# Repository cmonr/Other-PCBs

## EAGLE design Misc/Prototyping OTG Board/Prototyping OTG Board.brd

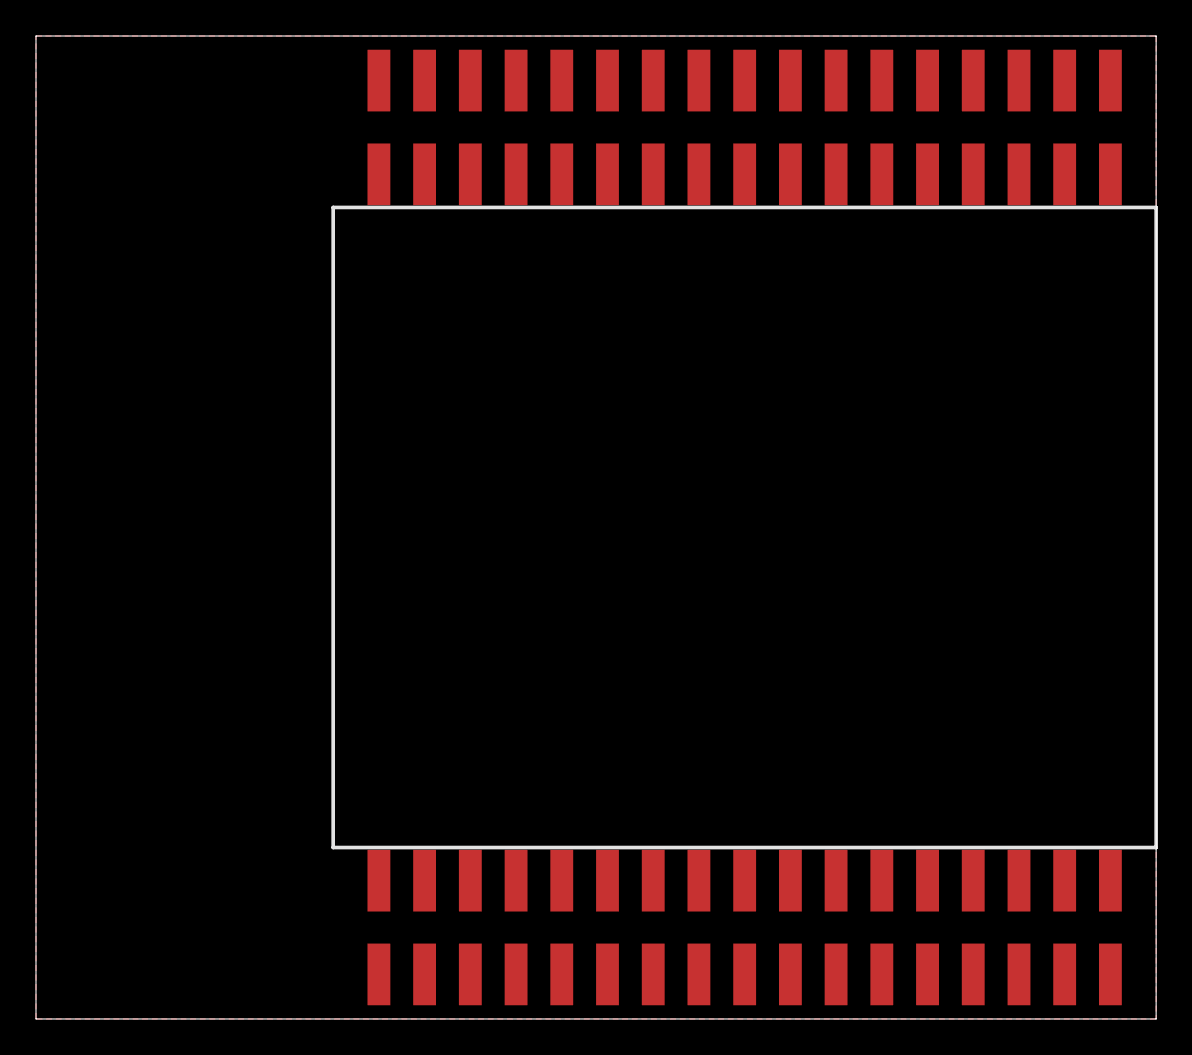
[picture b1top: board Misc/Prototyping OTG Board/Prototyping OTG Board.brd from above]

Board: 2 copper layers, 62.2 x 54.6 mm, 4 parts (0 on the bottom side), 2 nets, no tracks yet.

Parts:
U$2: BREADBOARDMINI; BREADBOARD-MINI
U$3: LIPO-OUTLINE2000; LIPO-2000
U$4, U$5: SSW-117-22-XXX-D-VS

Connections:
GND: U$4.18, U$4.19, U$4.20, U$4.21, U$4.22, U$4.23, U$4.24, U$4.25, U$4.26, U$4.27, U$4.28, U$4.29, U$4.30, U$4.31, U$4.32, U$4.33, U$4.34, U$5.18, U$5.19, U$5.20, U$5.21, U$5.22, U$5.23, U$5.24, U$5.25, U$5.26, U$5.27, U$5.28, U$5.29, U$5.30, U$5.31, U$5.32, U$5.33, U$5.34
VCC: U$4.1, U$4.2, U$4.3, U$4.4, U$4.5, U$4.6, U$4.7, U$4.8, U$4.9, U$4.10, U$4.11, U$4.12, U$4.13, U$4.14, U$4.15, U$4.16, U$4.17, U$5.1, U$5.2, U$5.3, U$5.4, U$5.5, U$5.6, U$5.7, U$5.8, U$5.9, U$5.10, U$5.11, U$5.12, U$5.13, U$5.14, U$5.15, U$5.16, U$5.17

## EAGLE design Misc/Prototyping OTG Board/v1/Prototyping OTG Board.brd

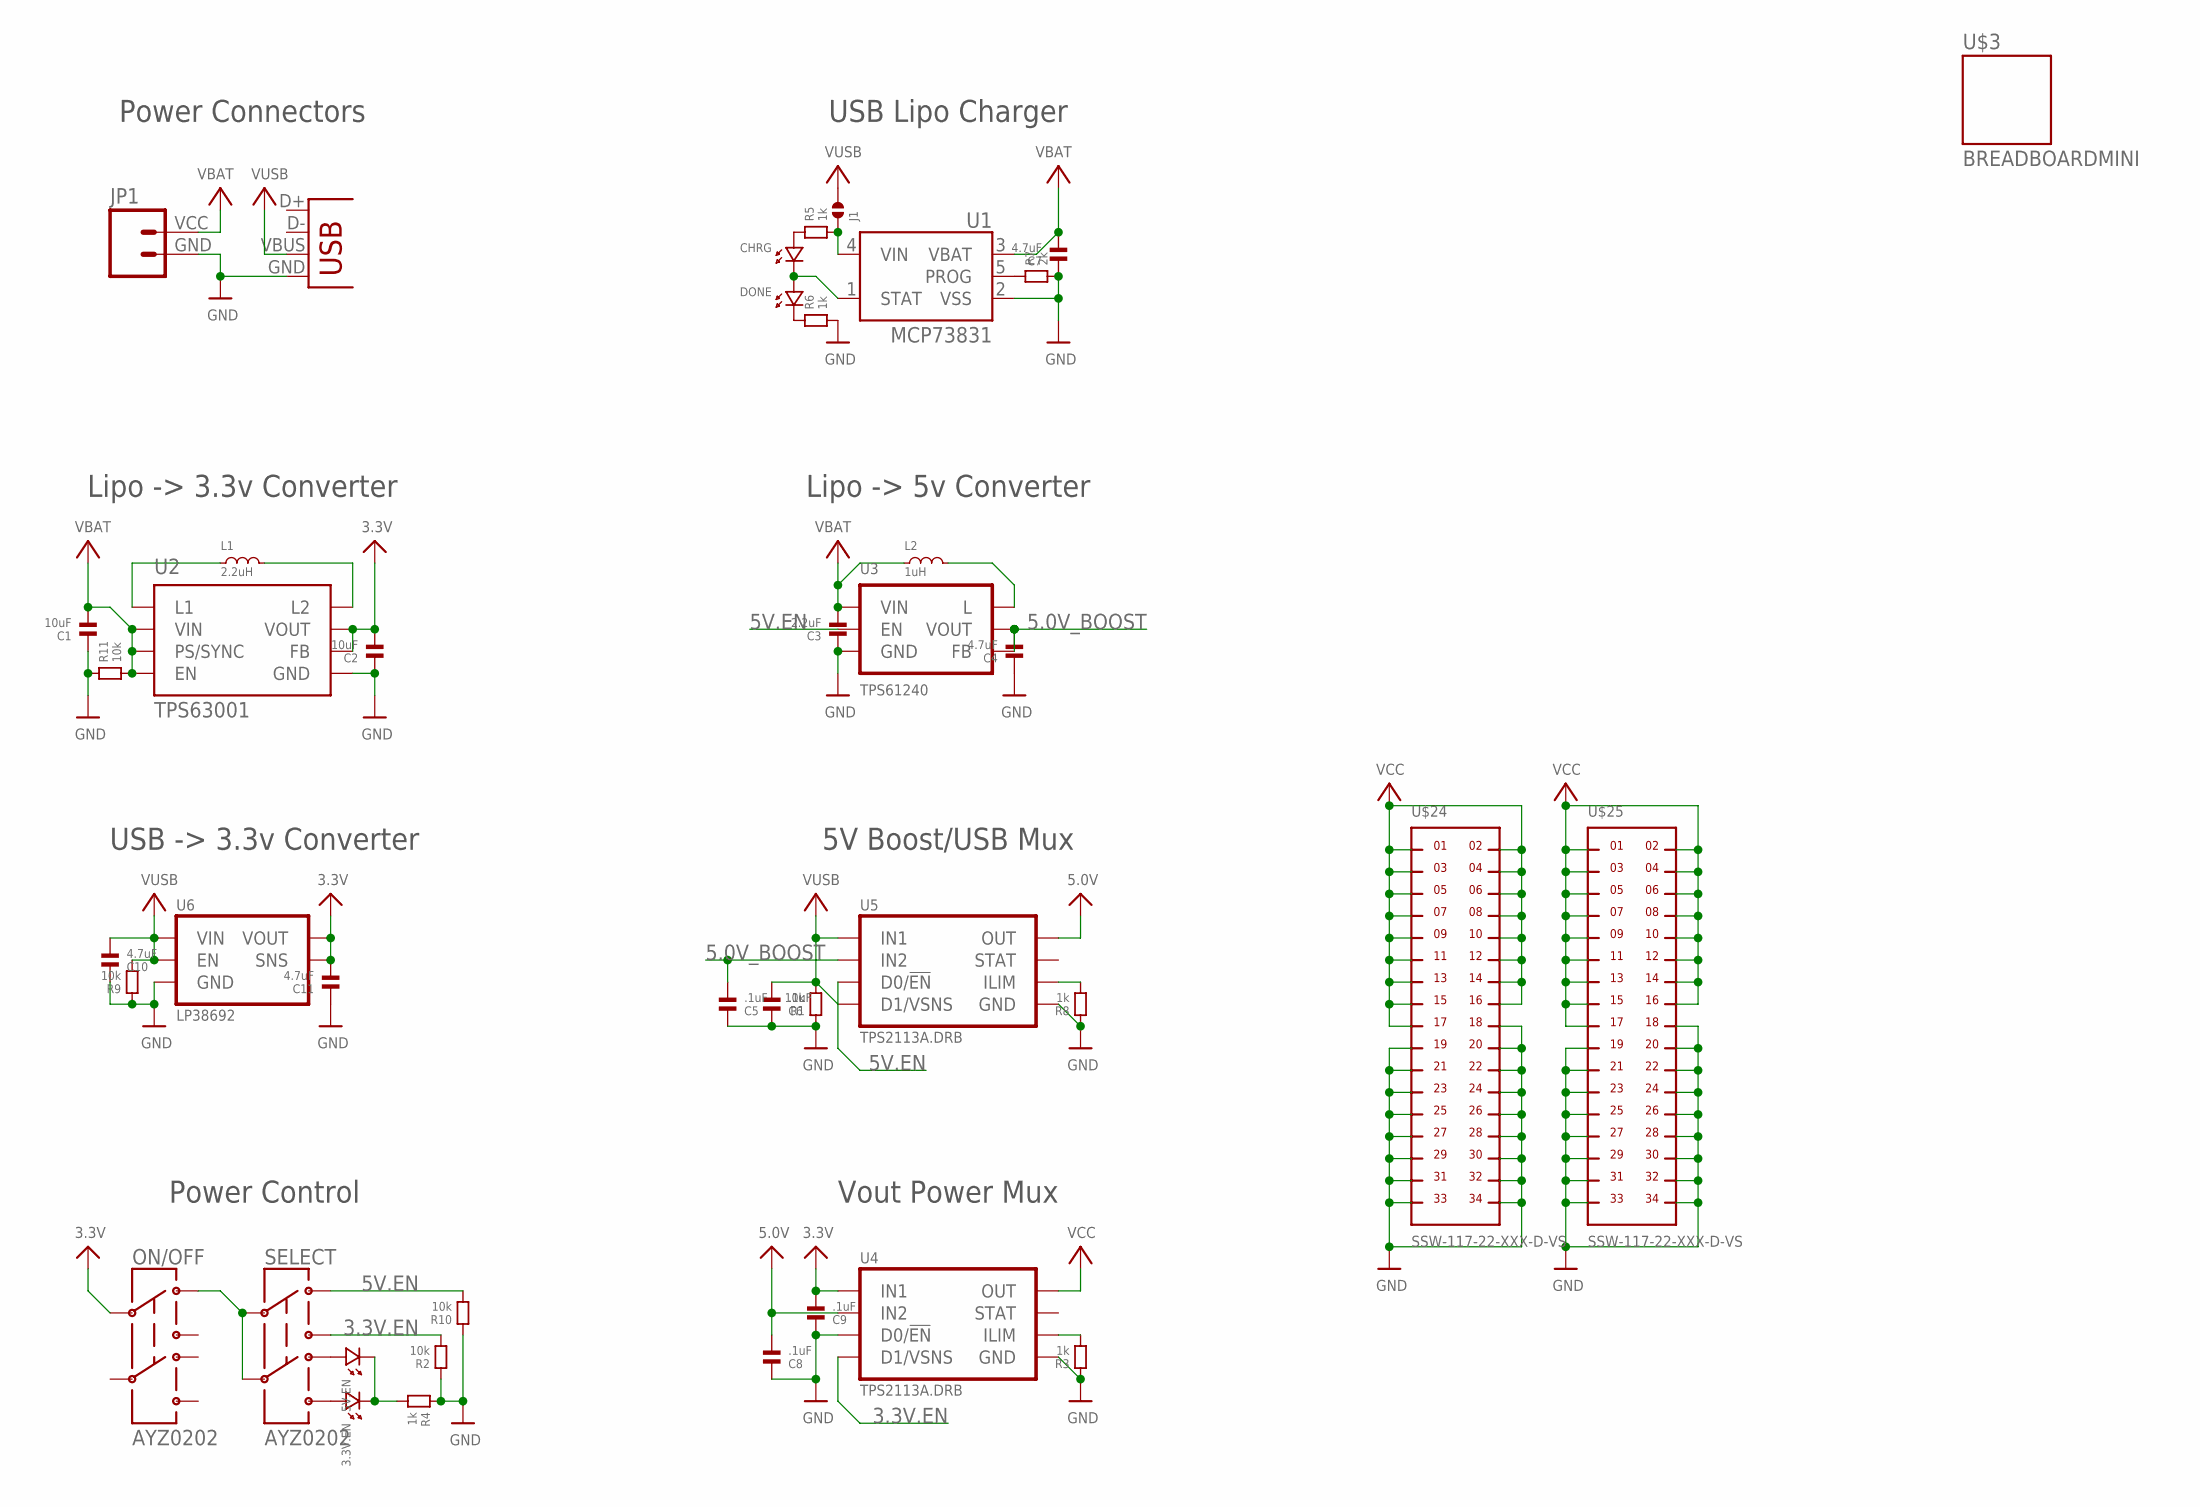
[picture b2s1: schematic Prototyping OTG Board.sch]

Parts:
3.3V.EN, 5V.EN: LED.0603; 0603.LED
C1, C2: 10uF; 0603
C3: 2.2uF; 0603
C4, C7, C10, C11: 4.7uF; 0603
C5, C6, C8, C9: .1uF; 0603
CHRG: LED.0603; 0603.LED
DONE: LED.0603; 0603.LED
J1: SOLDERJUMPER.2.LRG.PASTE; 2.LRG.PASTE
JP1: M024UCON-15767; JST-2-SMD-VERT
L1: 2.2uH; LQH3NP_M0
L2: 1uH; 0806.(2016)
ON/OFF: AYZ0202
R1, R2, R9, R10, R11: 10k; 0603
R3, R4, R5, R6, R8: 1k; 0603
R7: 2k; 0603
SELECT: AYZ0202
U1: MCP73831; SOT23-5
U2: TPS63001; DRC-S-PVSON-N10
U3: TPS61240; DRV
U4, U5: TPS2113A.DRB; DRB-S-PVSON-N8
U6: LP38692; LLP6
U$3: BREADBOARDMINI; BREADBOARD-MINI
U$24, U$25: SSW-117-22-XXX-D-VS
X1: USBSMD; USB-MINIB

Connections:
3.3V: C2.2, C9.2, C11.2, ON/OFF.2, U2.1 (VOUT), U2.10 (FB), U4.8 (IN1), U6.4 (VOUT), U6.5 (SNS)
3.3V.EN: R2.2, SELECT.1 (3), U4.3 (D1/VSNS)
5.0V: C8.2, U4.6 (IN2), U5.7 (OUT)
5.0V_BOOST: C4.2, C5.2, U3.2 (VOUT), U3.3 (FB), U5.6 (IN2)
5V.EN: R10.2, SELECT.3 (1), U3.4 (EN), U5.2 (D0/!EN)
GND: C1.1, C2.1, C3.1, C4.1, C5.1, C6.1, C7.1, C8.1, C9.1, C10.1, C11.1, JP1.GND (1), R1.1, R2.1, R3.1, R4.1, R6.2, R7.2, R8.1, R9.1, R10.1, R11.1, U1.2 (VSS), U2.3 (GND), U2.9 (GND), U2.TH (GND), U2.TH@1 (GND), U2.TH@2 (GND), U3.1 (GND), U3.PAD (GND), U4.2 (D0/!EN), U4.5 (GND), U4.TH (GND), U4.TH@1 (GND), U4.TH@2 (GND), U5.5 (GND), U5.TH (GND), U5.TH@1 (GND), U5.TH@2 (GND), U6.2 (GND), U6.PAD (GND), U$24.18, U$24.19, U$24.20, U$24.21, U$24.22, U$24.23, U$24.24, U$24.25, U$24.26, U$24.27, U$24.28, U$24.29, U$24.30, U$24.31, U$24.32, U$24.33, U$24.34, U$25.18, U$25.19, U$25.20, U$25.21, U$25.22, U$25.23, U$25.24, U$25.25, U$25.26, U$25.27, U$25.28, U$25.29, U$25.30, U$25.31, U$25.32, U$25.33, U$25.34, X1.GND
unnamed: R7.1, U1.5 (PROG)
unnamed: 5V.EN.P$1 (1), SELECT.6 (4)
unnamed: L1.1, U2.4 (L1)
unnamed: DONE.P$2 (2), R6.1
unnamed: CHRG.P$1 (1), R5.1
unnamed: CHRG.P$2 (2), DONE.P$1 (1), U1.1 (STAT)
unnamed: J1.1, R5.2, U1.4 (VIN)
unnamed: 3.3V.EN.P$1 (1), SELECT.4 (6)
unnamed: R3.2, U4.4 (ILIM)
unnamed: L1.2, U2.2 (L2)
unnamed: R8.2, U5.4 (ILIM)
unnamed: ON/OFF.3 (1), SELECT.2, SELECT.5
unnamed: 3.3V.EN.P$2 (2), 5V.EN.P$2 (2), R4.2
unnamed: L2.2, U3.5 (L)
VBAT: C1.2, C3.2, C7.2, JP1.VCC (2), L2.1, R11.2, U1.3 (VBAT), U2.5 (VIN), U2.6 (EN), U2.7 (PS/SYNC), U2.8 (VIN), U3.6 (VIN)
VCC: U4.7 (OUT), U$24.1, U$24.2, U$24.3, U$24.4, U$24.5, U$24.6, U$24.7, U$24.8, U$24.9, U$24.10, U$24.11, U$24.12, U$24.13, U$24.14, U$24.15, U$24.16, U$24.17, U$25.1, U$25.2, U$25.3, U$25.4, U$25.5, U$25.6, U$25.7, U$25.8, U$25.9, U$25.10, U$25.11, U$25.12, U$25.13, U$25.14, U$25.15, U$25.16, U$25.17
VDD: C6.2, C10.2, J1.2, R1.2, R9.2, U5.3 (D1/VSNS), U5.8 (IN1), U6.1 (VIN), U6.3 (EN), U6.6 (VIN), X1.VBUS

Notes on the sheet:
USB Lipo Charger
Lipo -> 3.3v Converter
Lipo -> 5v Converter
Power Connectors
5V Boost/USB Mux
Vout Power Mux
USB -> 3.3v Converter
Power Control

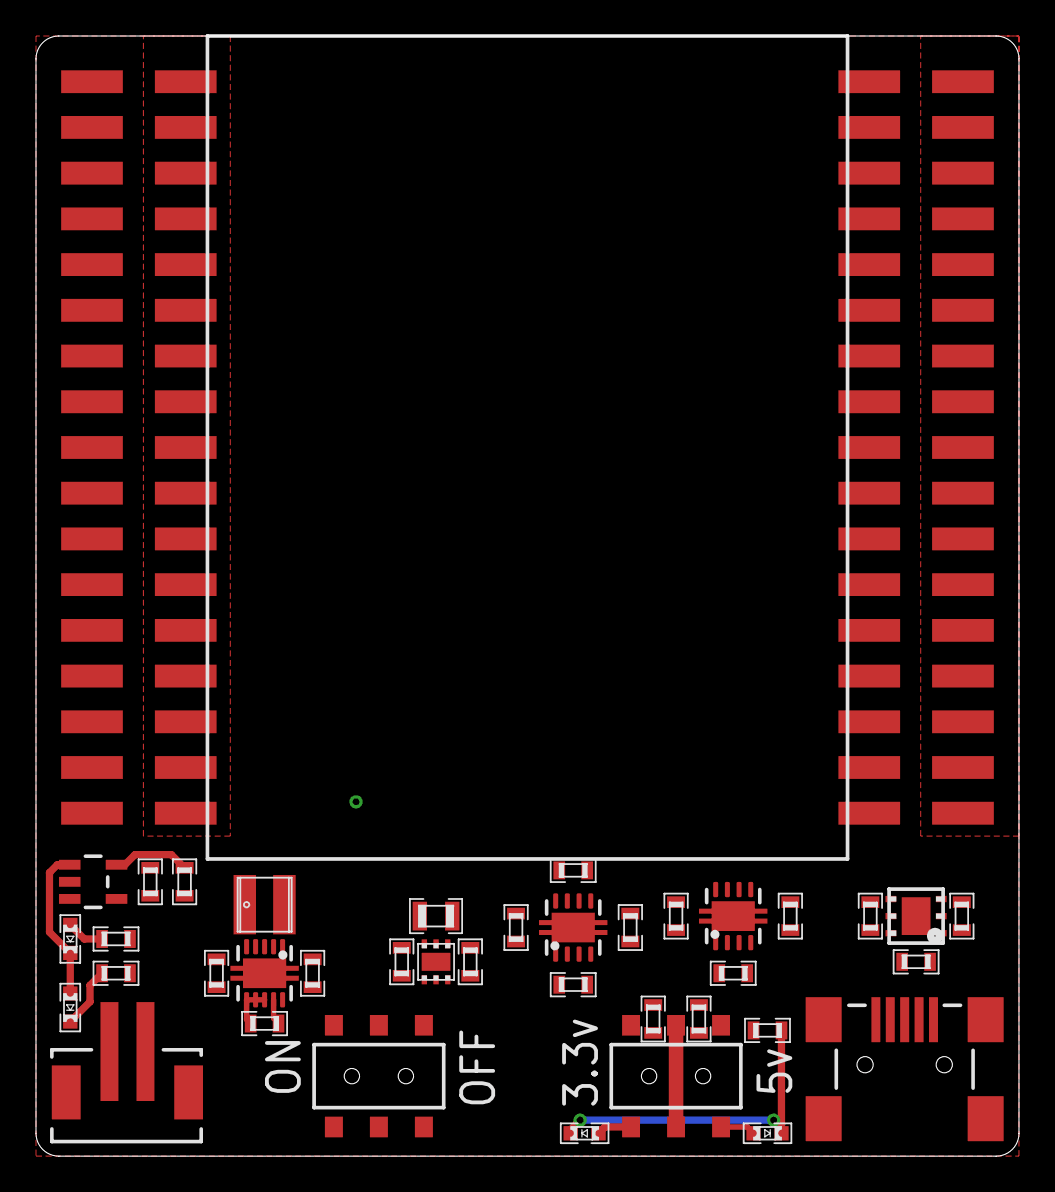
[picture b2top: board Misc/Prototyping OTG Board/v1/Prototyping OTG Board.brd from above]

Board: 2 copper layers, 54.6 x 62.2 mm, 42 parts (1 on the bottom side), 23 nets.

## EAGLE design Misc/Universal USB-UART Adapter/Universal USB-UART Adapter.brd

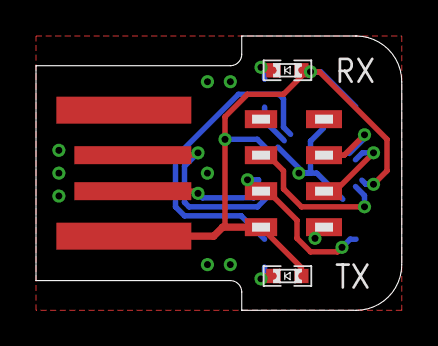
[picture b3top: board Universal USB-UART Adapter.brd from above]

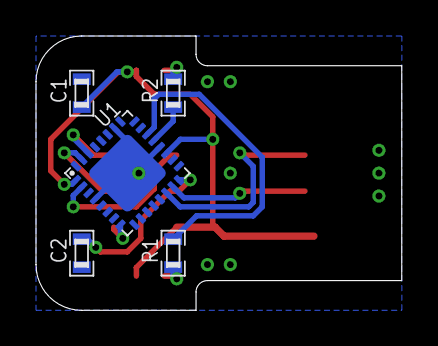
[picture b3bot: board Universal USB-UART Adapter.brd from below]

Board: 2 copper layers, 20.3 x 15.2 mm, 9 parts (5 on the bottom side), 13 nets.

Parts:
C1: .1uF; 0603
C2: 4.7uF; 0603
R1, R2: 1k; 0603
RX: 0603.LED
TX: 0603.LED
U1: FT232RQ; QFN32
U$4: MMT-104-01-X-DH-X
X1: USBPCB; USB-A-PCB

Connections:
3.3V: C2.1, U1.16, U$4.5
5.0V: C1.2, RX.P$1, TX.P$1, U1.1, U1.19, U$4.7, X1.5V
!CTS: U1.8, U$4.8
!DTR: U1.31, U$4.6
D+: U1.14, X1.USB_P
D-: U1.15, X1.USB_M
GND: C1.1, C2.2, U1.4, U1.17, U1.20, U1.24, U1.26, U1.EXP, U$4.1, X1.GND
unnamed: R2.1, RX.P$2
unnamed: R1.2, U1.22
unnamed: R1.1, TX.P$2
unnamed: R2.2, U1.21
RXI: U1.2, U$4.3
TXO: U1.30, U$4.4

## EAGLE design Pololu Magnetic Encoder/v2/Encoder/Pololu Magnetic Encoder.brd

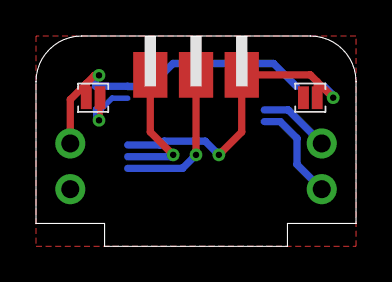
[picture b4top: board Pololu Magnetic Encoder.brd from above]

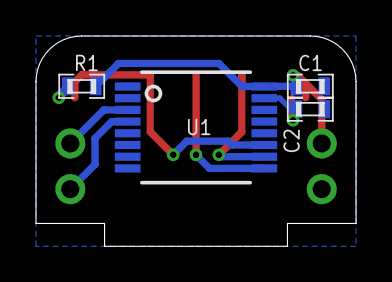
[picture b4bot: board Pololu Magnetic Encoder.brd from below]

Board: 2 copper layers, 17.8 x 11.7 mm, 9 parts (4 on the bottom side), 8 nets.

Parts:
C1: .1uF; 0603
C2: 2.2uF; 0603
J1, J2: 2.LRG.PASTE
JP1, JP2: 1X02_ROUND
R1: 100k; 0603
U1: AS5035; SSOP16
U$9: 1X3.SIDE

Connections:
!CS: J2.2, R1.2, U1.11, U$9.3
A: JP2.2, U1.3
B: JP2.1, U1.4
CLK: U1.10, U$9.1
DO: U1.9, U$9.2
GND: C1.2, C2.2, J2.1, JP1.1, U1.7
unnamed: C2.1, J1.1, U1.15
VIN: C1.1, J1.2, JP1.2, R1.1, U1.16

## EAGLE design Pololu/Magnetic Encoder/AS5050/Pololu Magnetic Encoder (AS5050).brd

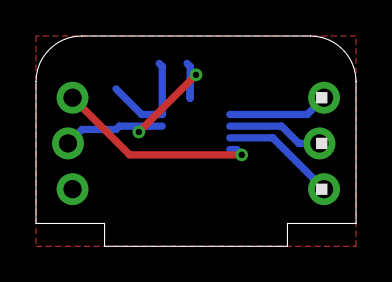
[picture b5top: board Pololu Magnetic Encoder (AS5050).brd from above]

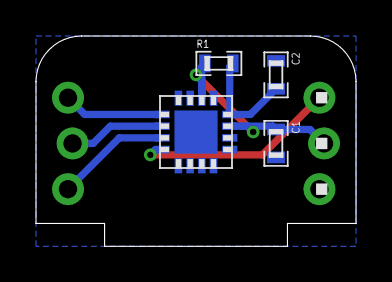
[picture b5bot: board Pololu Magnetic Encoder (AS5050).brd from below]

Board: 2 copper layers, 17.8 x 11.7 mm, 6 parts (5 on the bottom side), 7 nets.

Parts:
C1: 1uF; 0603
C2: 4.7uF; 0603
R1: 15; 0603
U1: AS5050.QFN; QFN.16
U$4, U$5: 1X3.LOCK

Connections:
3.3V: C1.1, R1.1, U1.11, U1.14, U$4.2
!CS: U1.4, U$4.1
GND: C1.2, C2.1, U1.9, U1.10, U1.13, U$4.3
MISO: U1.2, U$5.2
MOSI: U1.1, U$5.3
unnamed: C2.2, R1.2, U1.12
SCLK: U1.3, U$5.1

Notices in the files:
parts and their libraries:
microbuilder: This work is placed in the public domain, and may be freely used for commercial and non-commercial work with the following conditions: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
